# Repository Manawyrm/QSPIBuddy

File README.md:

QSPIBuddy - SPI NOR Flash Mux
============================

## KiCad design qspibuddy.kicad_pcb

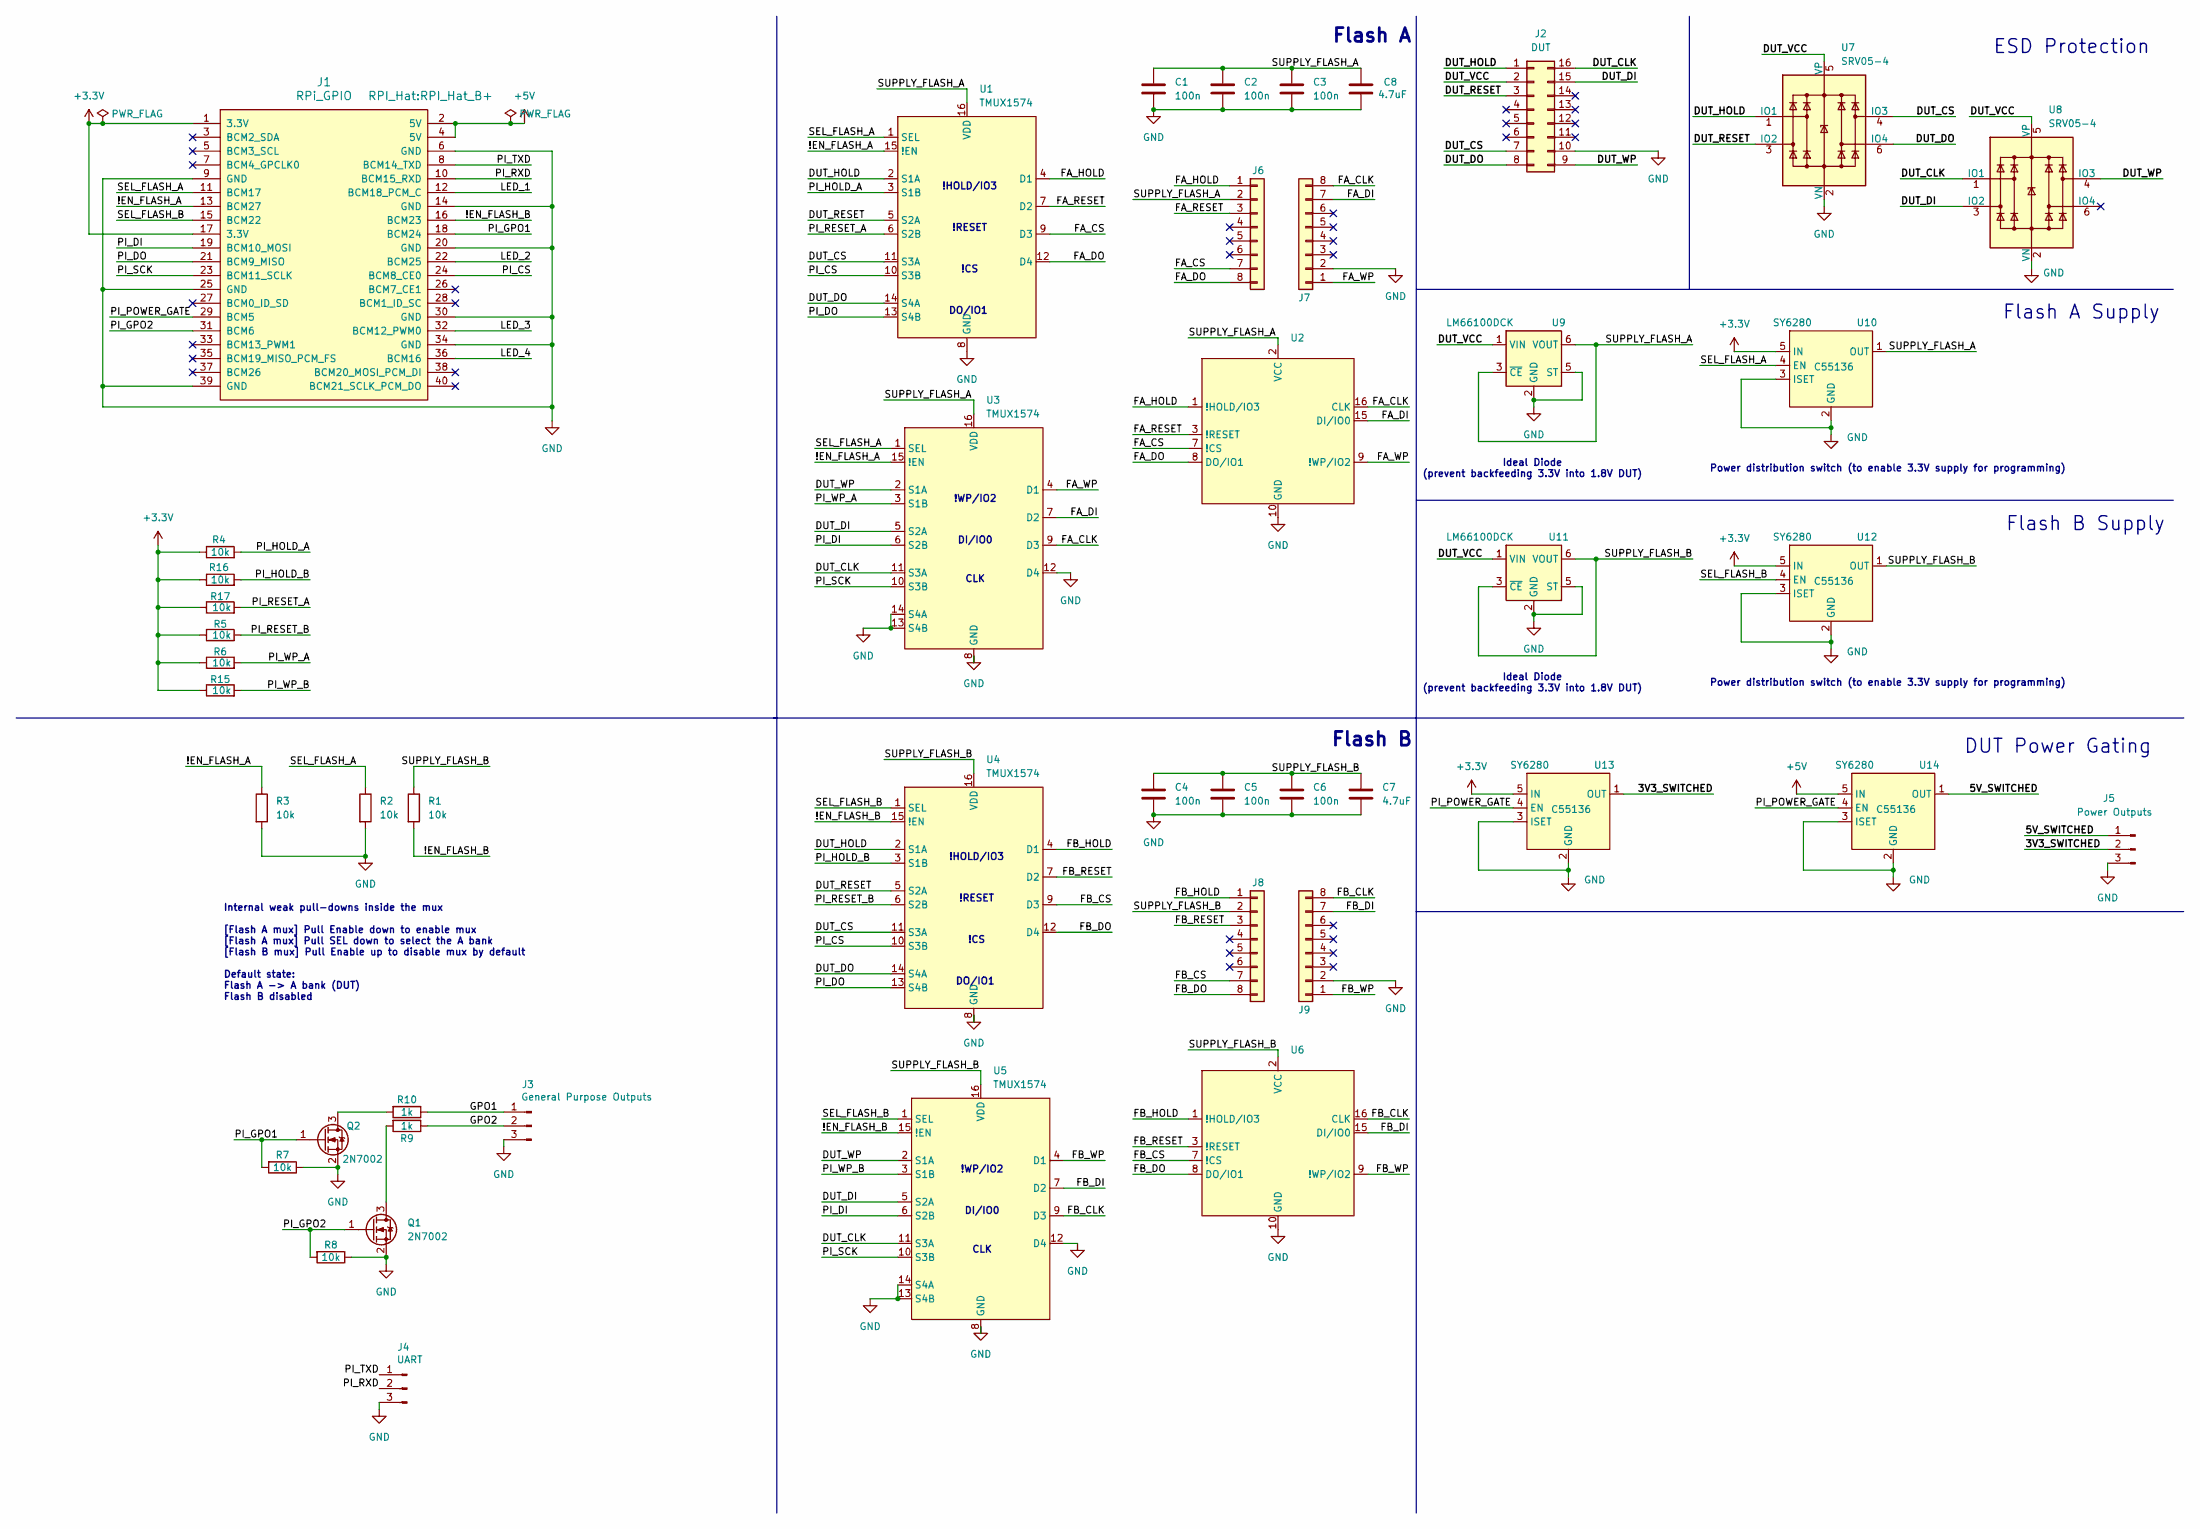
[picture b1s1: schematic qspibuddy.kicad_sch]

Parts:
C1, C2, C3, C4, C5, C6: 100n; C_0402_1005Metric; LCSC C1525
C7, C8: 4.7uF; C_0805_2012Metric; LCSC C1779
J1: RPi_GPIO; RPI_Hat_B+
J2: DUT; Hirose_FH12-16S-0.5SH_1x16-1MP_P0.50mm_Horizontal; LCSC C262665
J3: General Purpose Outputs; PinHeader_1x03_P2.54mm_Vertical
J4: UART; PinHeader_1x03_P2.54mm_Vertical
J5: Power Outputs; PinHeader_1x03_P2.54mm_Vertical
J6, J7, J8, J9: Conn_01x08; PinHeader_1x08_P2.54mm_Vertical
Q1, Q2: 2N7002; SOT-23; LCSC C8545
R1, R2, R3, R4, R5, R6, R7, R8, R15, R16, R17: 10k; R_0402_1005Metric; LCSC C25744
R9, R10: 1k; R_0402_1005Metric; LCSC C11702
U1, U3, U4, U5: TMUX1574; Texas_DYY0016A_TSOT-23-16_4.2x2.0mm_P0.5mm; LCSC C1855769
U2, U6: G6179-07
U7, U8: SRV05-4; SOT-23-6; LCSC C558418
U9, U11: LM66100DCK; SOT-363_SC-70-6; LCSC C2869734
U10, U12, U13, U14: SY6280; SOT-23-5; LCSC C55136

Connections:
+3.3V: J1.1 (3.3V), J1.17 (3.3V), R4.1, R5.1, R6.1, R15.1, R16.1, R17.1, U10.5 (IN), U12.5 (IN), U13.5 (IN)
+5V: J1.2 (5V), J1.4 (5V), U14.5 (IN)
/3V3_SWITCHED: J5.2, U13.1 (OUT)
/5V_SWITCHED: J5.1, U14.1 (OUT)
/!EN_FLASH_A: J1.13 (BCM27), R3.1, U1.15 (!EN), U3.15 (!EN)
/!EN_FLASH_B: J1.16 (BCM23), R1.2, U4.15 (!EN), U5.15 (!EN)
/DUT_CLK: J2.16, U3.11 (S3A), U5.11 (S3A), U8.1 (IO1)
/DUT_CS: J2.7, U1.11 (S3A), U4.11 (S3A), U7.4 (IO3)
/DUT_DI: J2.15, U3.5 (S2A), U5.5 (S2A), U8.3 (IO2)
/DUT_DO: J2.8, U1.14 (S4A), U4.14 (S4A), U7.6 (IO4)
/DUT_HOLD: J2.1, U1.2 (S1A), U4.2 (S1A), U7.1 (IO1)
/DUT_RESET: J2.3, U1.5 (S2A), U4.5 (S2A), U7.3 (IO2)
/DUT_VCC: J2.2, U7.5 (VP), U8.5 (VP), U9.1 (VIN), U11.1 (VIN)
/DUT_WP: J2.9, U3.2 (S1A), U5.2 (S1A), U8.4 (IO3)
/FA_CLK: J7.8, U2.16 (CLK), U3.9 (D3)
/FA_CS: J6.7, U1.9 (D3), U2.7 (!CS)
/FA_DI: J7.7, U2.15 (DI/IO0), U3.7 (D2)
/FA_DO: J6.8, U1.12 (D4), U2.8 (DO/IO1)
/FA_HOLD: J6.1, U1.4 (D1), U2.1 (!HOLD/IO3)
/FA_RESET: J6.3, U1.7 (D2), U2.3 (!RESET)
/FA_WP: J7.1, U2.9 (!WP/IO2), U3.4 (D1)
/FB_CLK: J9.8, U5.9 (D3), U6.16 (CLK)
/FB_CS: J8.7, U4.9 (D3), U6.7 (!CS)
/FB_DI: J9.7, U5.7 (D2), U6.15 (DI/IO0)
/FB_DO: J8.8, U4.12 (D4), U6.8 (DO/IO1)
/FB_HOLD: J8.1, U4.4 (D1), U6.1 (!HOLD/IO3)
/FB_RESET: J8.3, U4.7 (D2), U6.3 (!RESET)
/FB_WP: J9.1, U5.4 (D1), U6.9 (!WP/IO2)
/GPO1: J3.1, R10.1
/GPO2: J3.2, R9.1
/LED_1: J1.12 (BCM18_PCM_C)
/LED_2: J1.22 (BCM25)
/LED_3: J1.32 (BCM12_PWM0)
/LED_4: J1.36 (BCM16)
/PI_CS: J1.24 (BCM8_CE0), U1.10 (S3B), U4.10 (S3B)
/PI_DI: J1.19 (BCM10_MOSI), U3.6 (S2B), U5.6 (S2B)
/PI_DO: J1.21 (BCM9_MISO), U1.13 (S4B), U4.13 (S4B)
/PI_GPO1: J1.18 (BCM24), Q2.1 (G), R7.2
/PI_GPO2: J1.31 (BCM6), Q1.1 (G), R8.2
/PI_HOLD_A: R4.2, U1.3 (S1B)
/PI_HOLD_B: R16.2, U4.3 (S1B)
/PI_POWER_GATE: J1.29 (BCM5), U13.4 (EN), U14.4 (EN)
/PI_RESET_A: R17.2, U1.6 (S2B)
/PI_RESET_B: R5.2, U4.6 (S2B)
/PI_RXD: J1.10 (BCM15_RXD), J4.2
/PI_SCK: J1.23 (BCM11_SCLK), U3.10 (S3B), U5.10 (S3B)
/PI_TXD: J1.8 (BCM14_TXD), J4.1
/PI_WP_A: R6.2, U3.3 (S1B)
/PI_WP_B: R15.2, U5.3 (S1B)
/SEL_FLASH_A: J1.11 (BCM17), R2.1, U1.1 (SEL), U3.1 (SEL), U10.4 (EN)
/SEL_FLASH_B: J1.15 (BCM22), U4.1 (SEL), U5.1 (SEL), U12.4 (EN)
/SUPPLY_FLASH_A: C1.1, C2.1, C3.1, C8.1, J6.2, U1.16 (VDD), U2.2 (VCC), U3.16 (VDD), U9.3 (~CE), U9.6 (VOUT), U10.1 (OUT)
/SUPPLY_FLASH_B: C4.1, C5.1, C6.1, C7.1, J8.2, R1.1, U4.16 (VDD), U5.16 (VDD), U6.2 (VCC), U11.3 (~CE), U11.6 (VOUT), U12.1 (OUT)
GND: C1.2, C2.2, C3.2, C4.2, C5.2, C6.2, C7.2, C8.2, J1.6 (GND), J1.9 (GND), J1.14 (GND), J1.20 (GND), J1.25 (GND), J1.30 (GND), J1.34 (GND), J1.39 (GND), J2.10, J3.3, J4.3, J5.3, J7.2, J9.2, Q1.2 (S), Q2.2 (S), R2.2, R3.2, R7.1, R8.1, U1.8 (GND), U2.10 (GND), U3.8 (GND), U3.12 (D4), U3.13 (S4B), U3.14 (S4A), U4.8 (GND), U5.8 (GND), U5.12 (D4), U5.13 (S4B), U5.14 (S4A), U6.10 (GND), U7.2 (VN), U8.2 (VN), U9.2 (GND), U9.5 (ST), U10.2 (GND), U10.3 (ISET), U11.2 (GND), U11.5 (ST), U12.2 (GND), U12.3 (ISET), U13.2 (GND), U13.3 (ISET), U14.2 (GND), U14.3 (ISET)
unnamed: Q1.3 (D), R9.2
unnamed: Q2.3 (D), R10.2

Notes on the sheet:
!HOLD/IO3
Flash B
Power distribution switch (to enable 3.3V supply for programming)
!RESET
Flash B Supply
Ideal Diode (prevent backfeeding 3.3V into 1.8V DUT)
CLK
ESD Protection
!CS
DO/IO1
Flash A Supply
DI/IO0
!WP/IO2
Flash A
DUT Power Gating
Internal weak pull-downs inside the mux [Flash A mux] Pull Enable down to enable mux [Flash A mux] Pull SEL down to select the A bank [Flash B mux] Pull Enable up to disable mux by default Default state: Flash A -> A bank (DUT) Flash B disabled

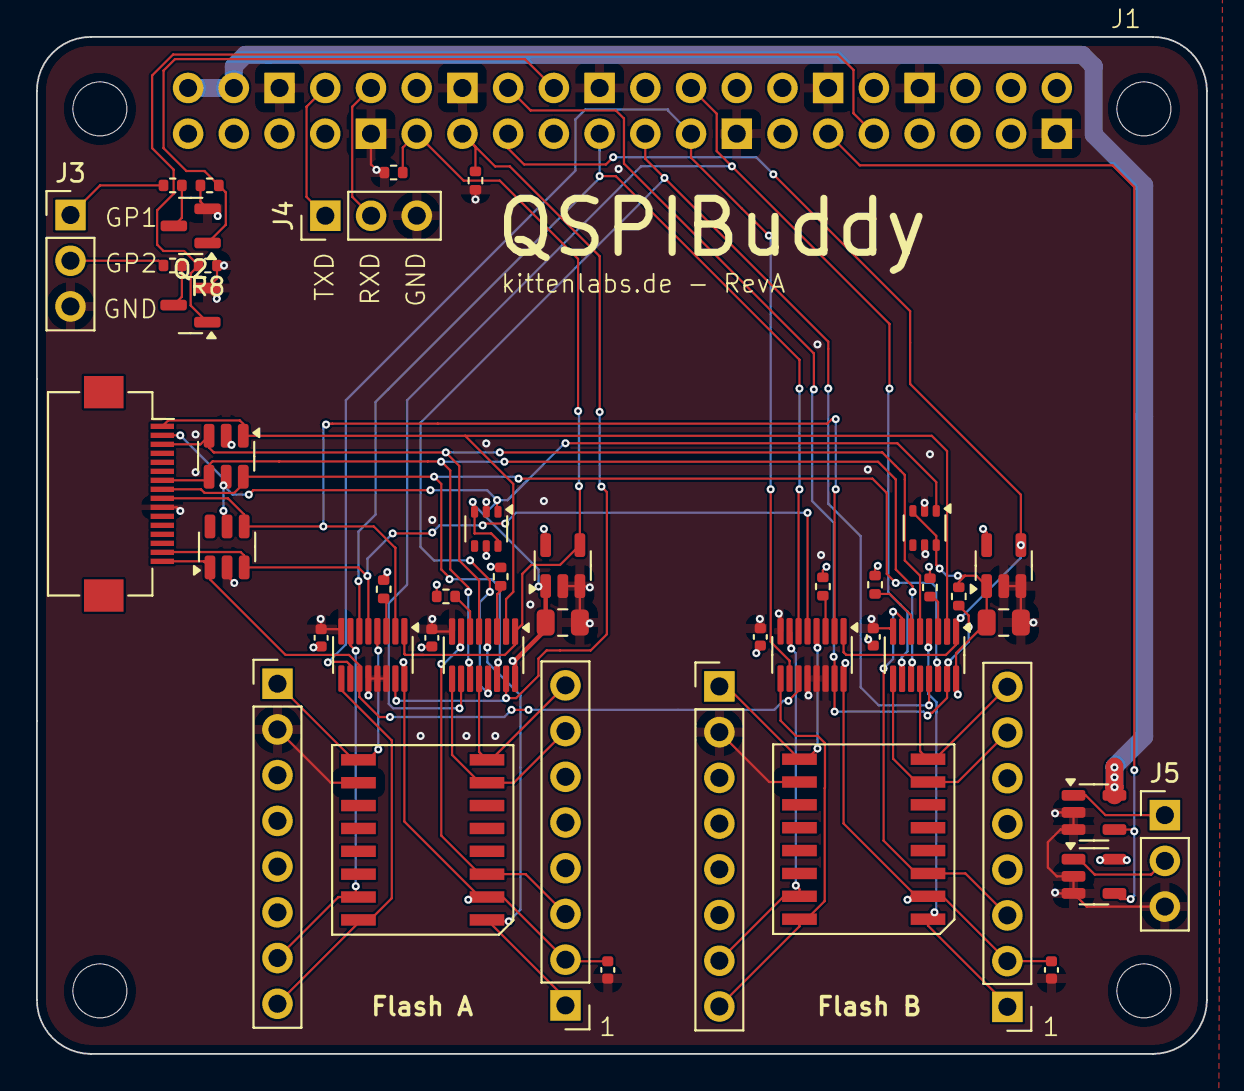
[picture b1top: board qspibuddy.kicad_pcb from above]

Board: 4 copper layers, 65.0 x 56.5 mm, 46 parts (0 on the bottom side), 52 nets.

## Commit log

2025-02-18 inital commit
2025-02-19 routed
